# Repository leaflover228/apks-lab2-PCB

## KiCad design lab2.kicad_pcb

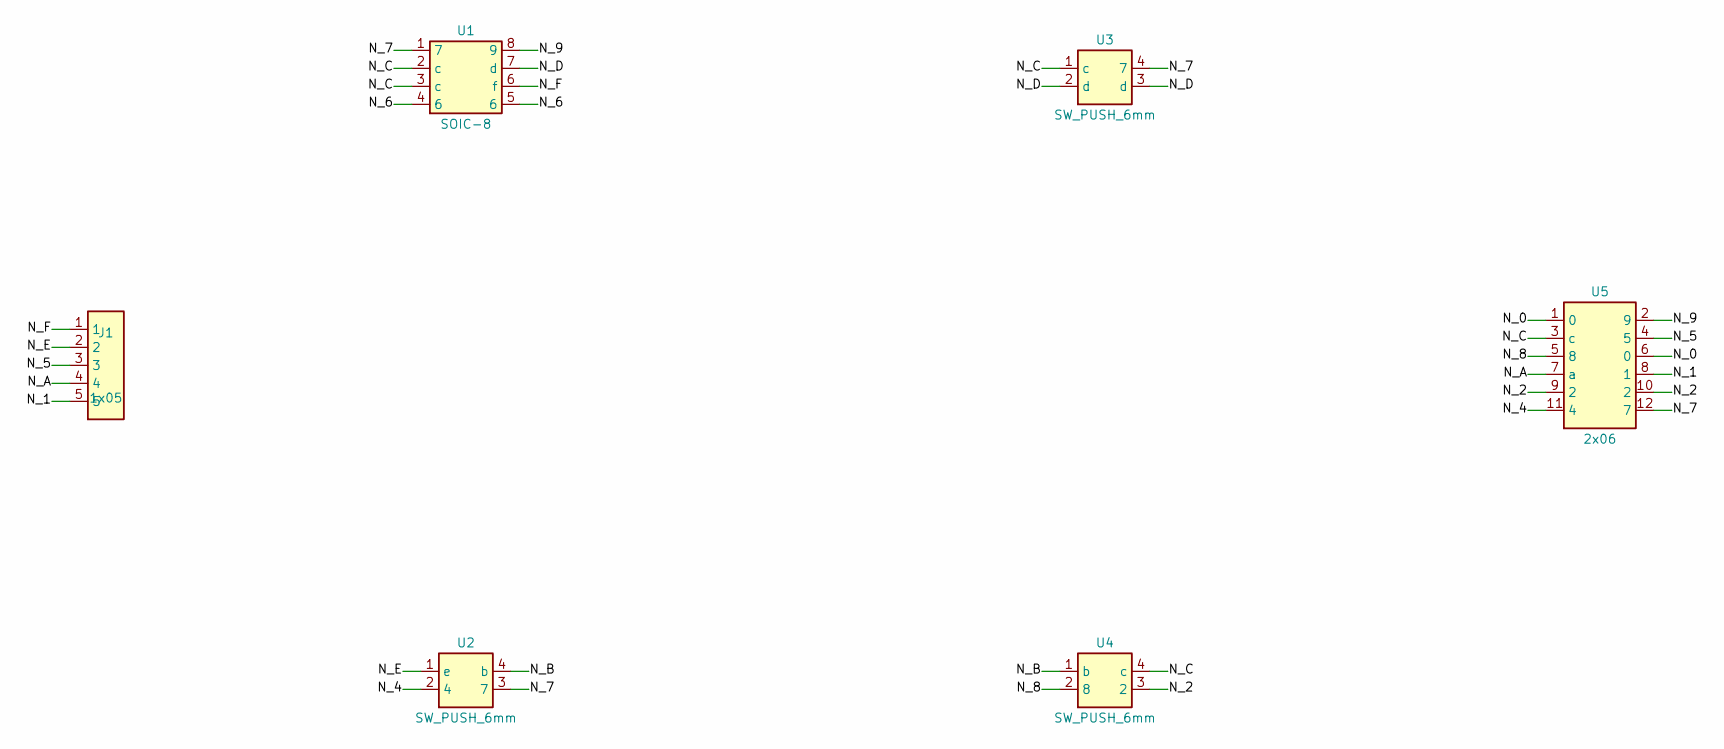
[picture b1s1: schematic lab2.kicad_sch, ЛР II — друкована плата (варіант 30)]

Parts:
J1: 1x05; J1_1x5_P2.54
U1: SOIC-8; U1_SOIC-8_P1.27
U2, U3, U4: SW_PUSH_6mm
U5: 2x06; U5_2x06_P2.54

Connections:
/N_0: U5.1 (0), U5.6 (0)
/N_1: J1.5, U5.8 (1)
/N_2: U4.3 (2), U5.9 (2), U5.10 (2)
/N_4: U2.2 (4), U5.11 (4)
/N_5: J1.3, U5.4 (5)
/N_6: U1.4 (6), U1.5 (6)
/N_7: U1.1 (7), U2.3 (7), U3.4 (7), U5.12 (7)
/N_8: U4.2 (8), U5.5 (8)
/N_9: U1.8 (9), U5.2 (9)
/N_A: J1.4, U5.7 (a)
/N_B: U2.4 (b), U4.1 (b)
/N_C: U1.2 (c), U1.3 (c), U3.1 (c), U4.4 (c), U5.3 (c)
/N_D: U1.7 (d), U3.2 (d), U3.3 (d)
/N_E: J1.2, U2.1 (e)
/N_F: J1.1, U1.6 (f)

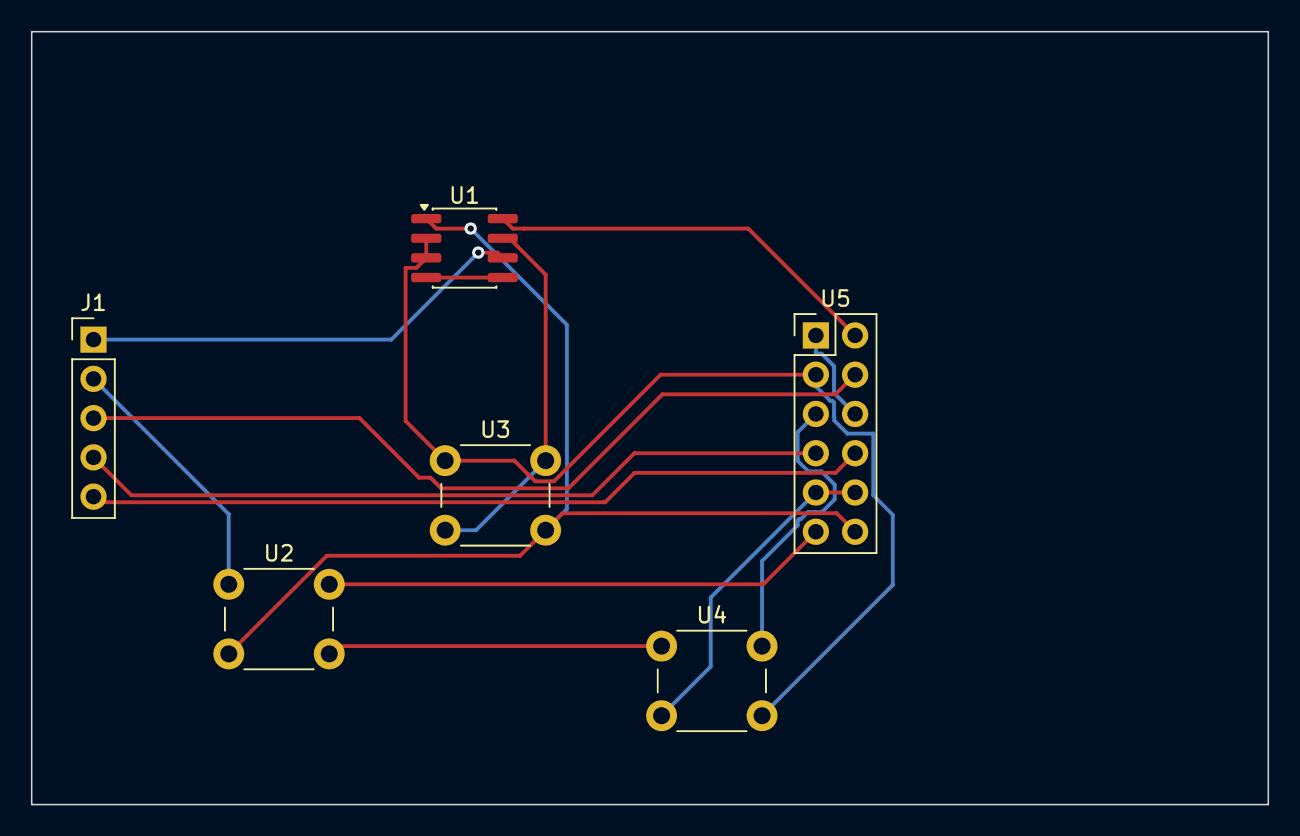
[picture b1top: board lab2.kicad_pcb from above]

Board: 2 copper layers, 80.0 x 50.0 mm, 6 parts (0 on the bottom side), 15 nets.
